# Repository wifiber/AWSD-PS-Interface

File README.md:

Atomiswave Sit Down (AWSD) arcade cabinet power supply interface board
==============

This PCB is an interface from the Meanwell QP-150-3A power supply to the stock wiring in the AWSD arcade cabinet.

The Meanwell QP-150-3A is a Quad-output PS (https://www.meanwell-web.com/en-gb/ac-dc-quad-output-enclosed-power-supply-output-qp--150--3a)
Providing 3.3V, 5V, 12V, -5V outputs

The AWSD arcade cabinet power supply is wired with a JST VH series connector for the input AC power and 2 Molex Mini-Fit JR Connectors for the output 3.3, 5, and 12 volt power.
5 conductor JST VH series (AC-N, AC-L, FG)
8 conductor Molex Mini-Fit (12V, GND)
12 conductor Molex Mini-Fit (3.3V, GND, 5V)

This interface board is designed to screw directly to the screw terminals on the Meanwell QP-150-3A. This board interfaces with the JST VH connector and the Molex Mini-Fit JR Connectors in the AWSD so no changes need to be made to the wiring harness.
There is mounting holes and solder points to add a small LCD voltage display - https://www.aliexpress.com/i/32840259666.html?spm=2114.12057483.0.0.206f62fepYHKGu
A switch can be used to switch 3.3 or 5 volts to the LCD voltage display for verification and tuning.

The AWSD arcade cabinet has 2 unused conductors in the 12-pin Molex connector. The stock AWSD power supply provides 3.3 volts on these pins that is never utilized inside the AWSD cabinet. 
I have included a 3-terminal jumper "JP1" on the interface board. It allows selection of 3.3V or -5V for these 2 pins. The rationale is that if you wanted to add the pins and wires to your AWSD arcade cabinet, you could add -5 Volt to the wiring harness and enjoy the games that require -5V.

An OSHPark Project for this board can be found here:
https://oshpark.com/shared_projects/lOjuucXz (0.5)
https://oshpark.com/shared_projects/chpeU0vp (0.4)

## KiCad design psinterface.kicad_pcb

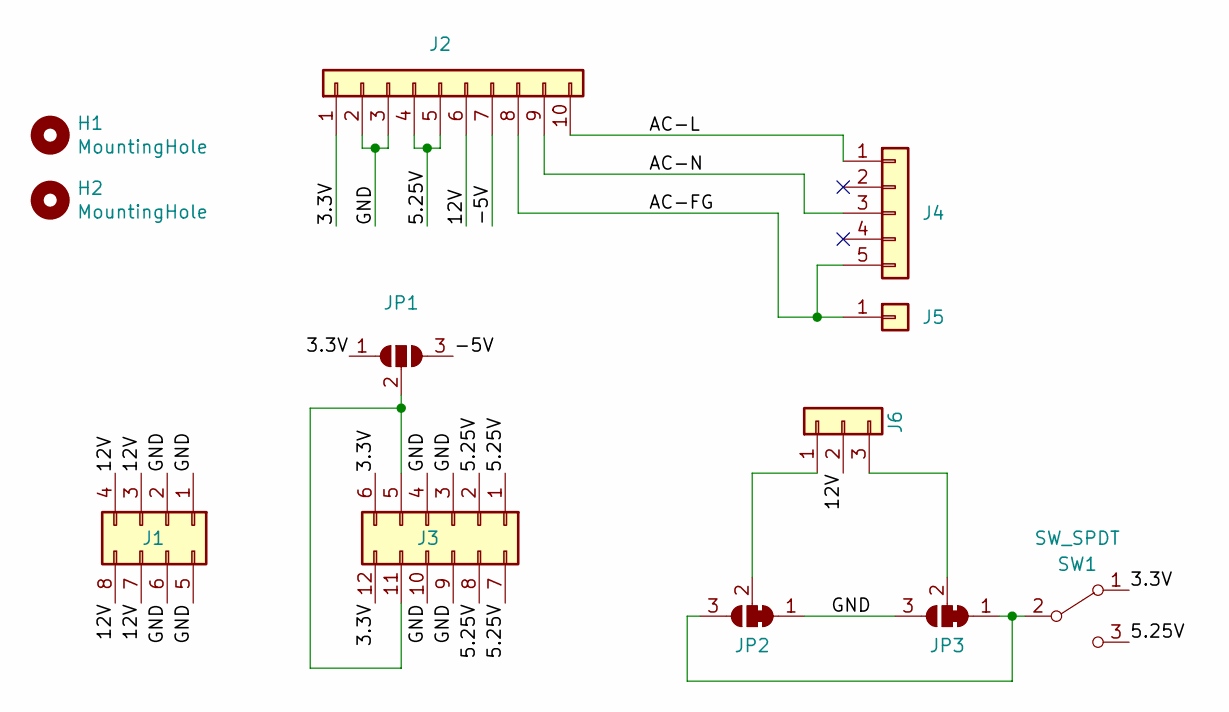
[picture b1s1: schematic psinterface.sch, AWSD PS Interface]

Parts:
H1, H2: MountingHole; MountingHole_2.7mm_M2.5
J1: Conn_02x04_Top_Bottom; Molex_Mini-Fit_Jr_5566-08A_2x04_P4.20mm_Vertical
J2: Conn_01x10; PSTabs_3.2mm_M3_DIN965_Pad
J3: Conn_02x06_Top_Bottom; Molex_Mini-Fit_Jr_5566-12A_2x06_P4.20mm_Vertical
J4: Conn_01x05; JST_VH_B5P-VH-FB-B_1x05_P3.96mm_Vertical
J5: Conn_01x01; MountingHole_4.3mm_M4_Pad_Via
J6: Conn_01x03; PinHeader_1x03_P2.54mm_Vertical
JP1: SolderJumper_3_Open; SolderJumper-3_P3.5mm_Open_Pad3.0x3.0mm
JP2, JP3: SolderJumper_3_Bridged12; SolderJumper-3_P1.3mm_Bridged12_RoundedPad1.0x1.5mm
SW1: SW_SPDT; SW_CuK_OS102011MA1QN1_SPDT_Angled

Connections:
/3.3V: J2.1, J3.6, J3.12, JP1.1 (A), SW1.1 (A)
/5.25V: J2.4, J2.5, J3.1, J3.2, J3.7, J3.8, SW1.3 (C)
/12V: J1.3, J1.4, J1.7, J1.8, J2.6, J6.2
/-5V: J2.7, JP1.3 (B)
/AC-FG: J2.8, J4.5, J5.1
/AC-L: J2.10, J4.1
/AC-N: J2.9, J4.3
/GND: J1.1, J1.2, J1.5, J1.6, J2.2, J2.3, J3.3, J3.4, J3.9, J3.10, JP2.1 (A), JP3.3 (B)
unnamed: J3.5, J3.11, JP1.2 (C)
unnamed: J6.1, JP2.2 (C)
unnamed: J6.3, JP3.2 (C)
unnamed: JP2.3 (B), JP3.1 (A), SW1.2 (B)

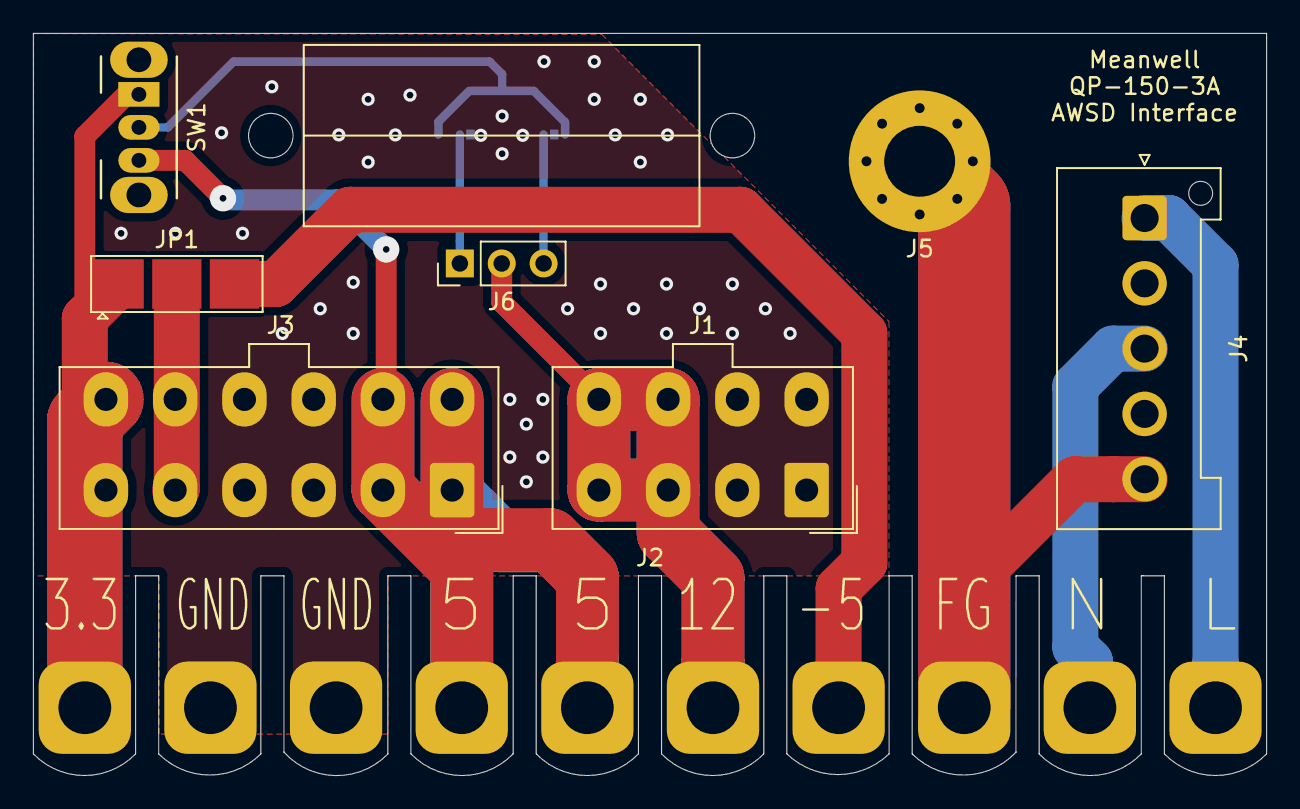
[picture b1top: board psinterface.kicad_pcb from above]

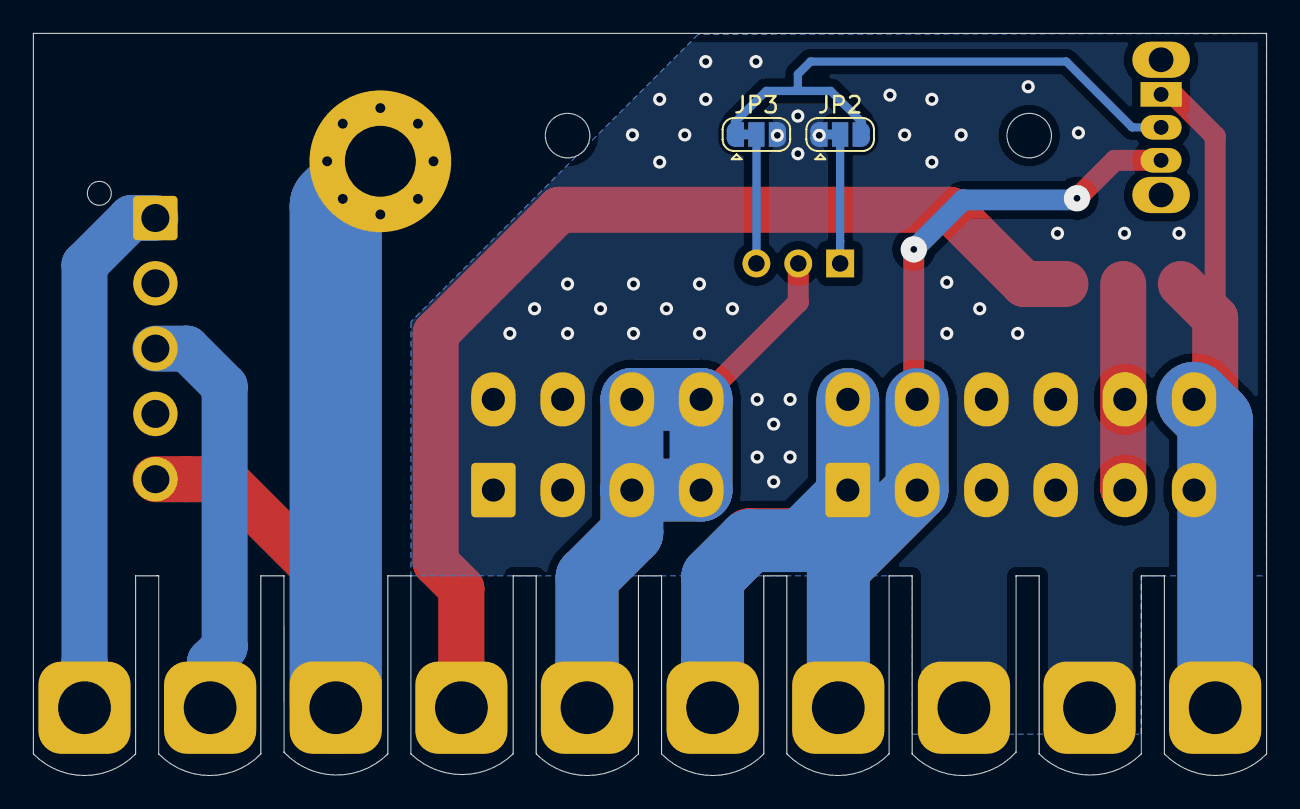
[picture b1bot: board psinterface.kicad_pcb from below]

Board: 2 copper layers, 74.8 x 45.0 mm, 12 parts (2 on the bottom side), 12 nets.

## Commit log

2020-02-08 Reduced sized, added text labels
2020-02-08 add readme
2020-02-08 Changed LCD mounting holes to 28mm
2020-02-08 Update OSHPark Link
2020-02-09 Corrected AC wiring, updated parts list
2020-02-09 Fix OSHpark link
2020-02-09 Mounting holes for LCD fixed
2020-02-09 OSH links
2020-02-09 Rounded flanges, fixed wiring
2020-02-09 Doc updated
2020-02-09 added binary files
2020-02-25 Better use of bottom copper
2020-03-04 J6 now 4MM, JP2/3 added to allow diff polarity LCD
2020-03-10 Fixed OSHPark link
2021-02-15 Corrected LCD default polarity, update silk screen
